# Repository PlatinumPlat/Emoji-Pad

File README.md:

# Emoji-Pad

# Description & Features
Emoji-Pad is a 5 key macropad with 2 WS2812B Leds. It uses KMK firmware and has five buttons for typing the common emojis: '👍', '🤣', '💀', '🔥', and '😃'.

# Bill Of Materials
Everything you need to make the Emoji-Pad!
- 5x Cherry MX Switches
- 4x M3x5x4 Heatset inserts
- 2x WS2812B LEDs
- 1x XIAO RP2040
- 1x Case (2 printed parts)

# Firmware
The Emoji-Pad uses KMK firmware (in Circuit Python) for all its components.
The 5 keys currently act as macros.

# Screenshots
Hackpad CAD model:
The top and bottom of the case fit together using 4 M3 Bolts and heatset inserts.

I made the Schematic and PCB in Kicad.

Schematic:

PCB:

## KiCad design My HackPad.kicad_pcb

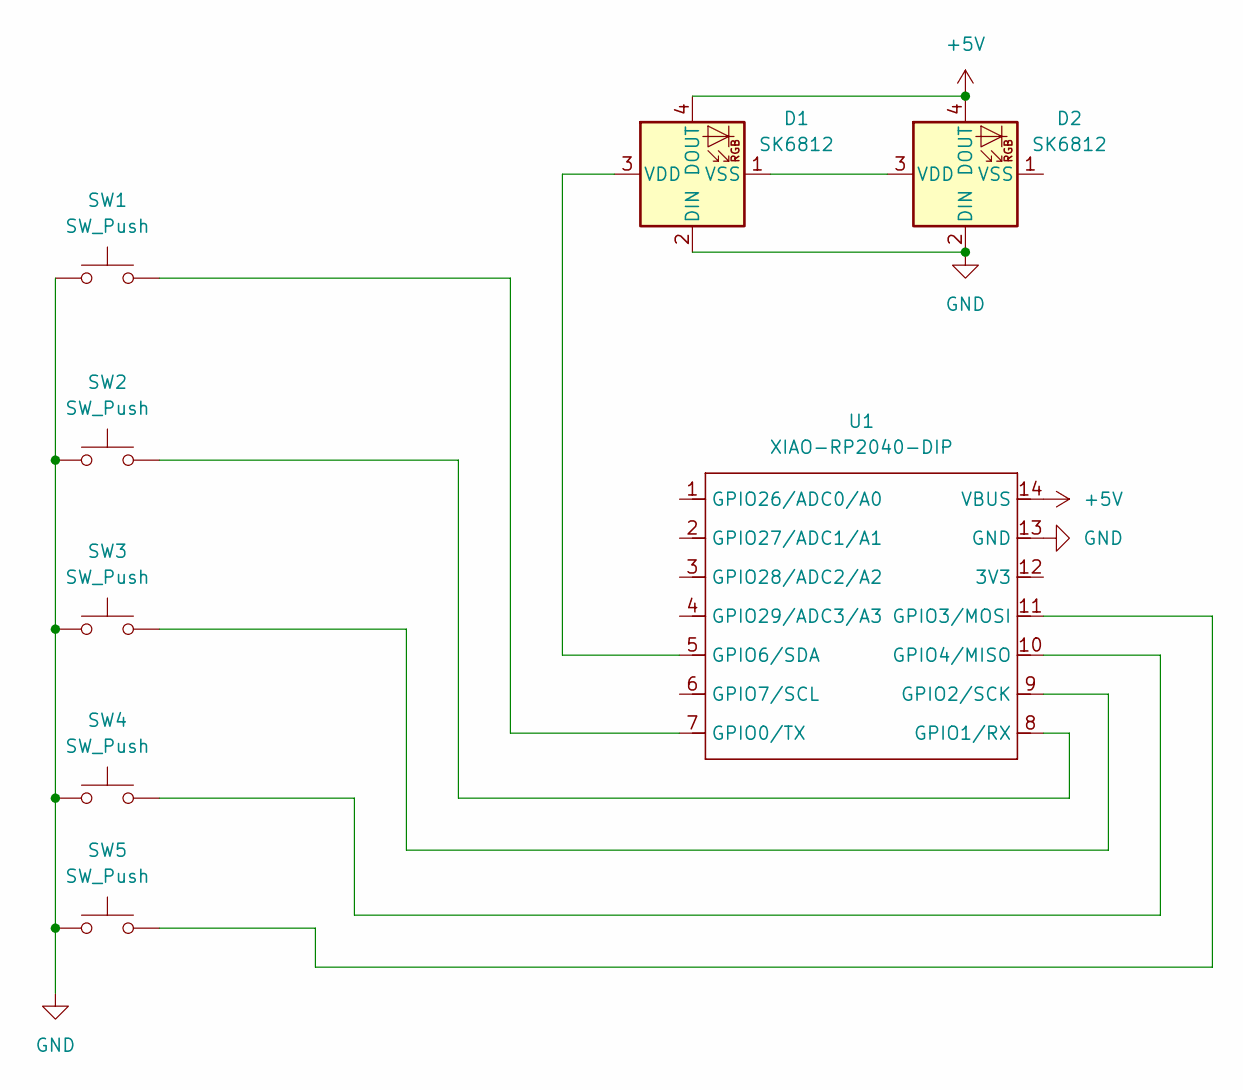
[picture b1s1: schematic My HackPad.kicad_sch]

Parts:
D1, D2: SK6812; LED_SK6812MINI_PLCC4_3.5x3.5mm_P1.75mm
SW1, SW2, SW3, SW4, SW5: SW_Push; SW_Cherry_MX_1.00u_PCB
U1: XIAO-RP2040-DIP

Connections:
+5V: D1.4 (DOUT), D2.4 (DOUT), U1.14 (VBUS)
GND: D1.2 (DIN), D2.2 (DIN), SW1.1, SW2.1, SW3.1, SW4.1, SW5.1, U1.13 (GND)
unnamed: D1.3 (VDD), U1.5 (GPIO6/SDA)
unnamed: D1.1 (VSS), D2.3 (VDD)
unnamed: SW1.2, U1.7 (GPIO0/TX)
unnamed: SW2.2, U1.8 (GPIO1/RX)
unnamed: SW3.2, U1.9 (GPIO2/SCK)
unnamed: SW5.2, U1.11 (GPIO3/MOSI)
unnamed: SW4.2, U1.10 (GPIO4/MISO)

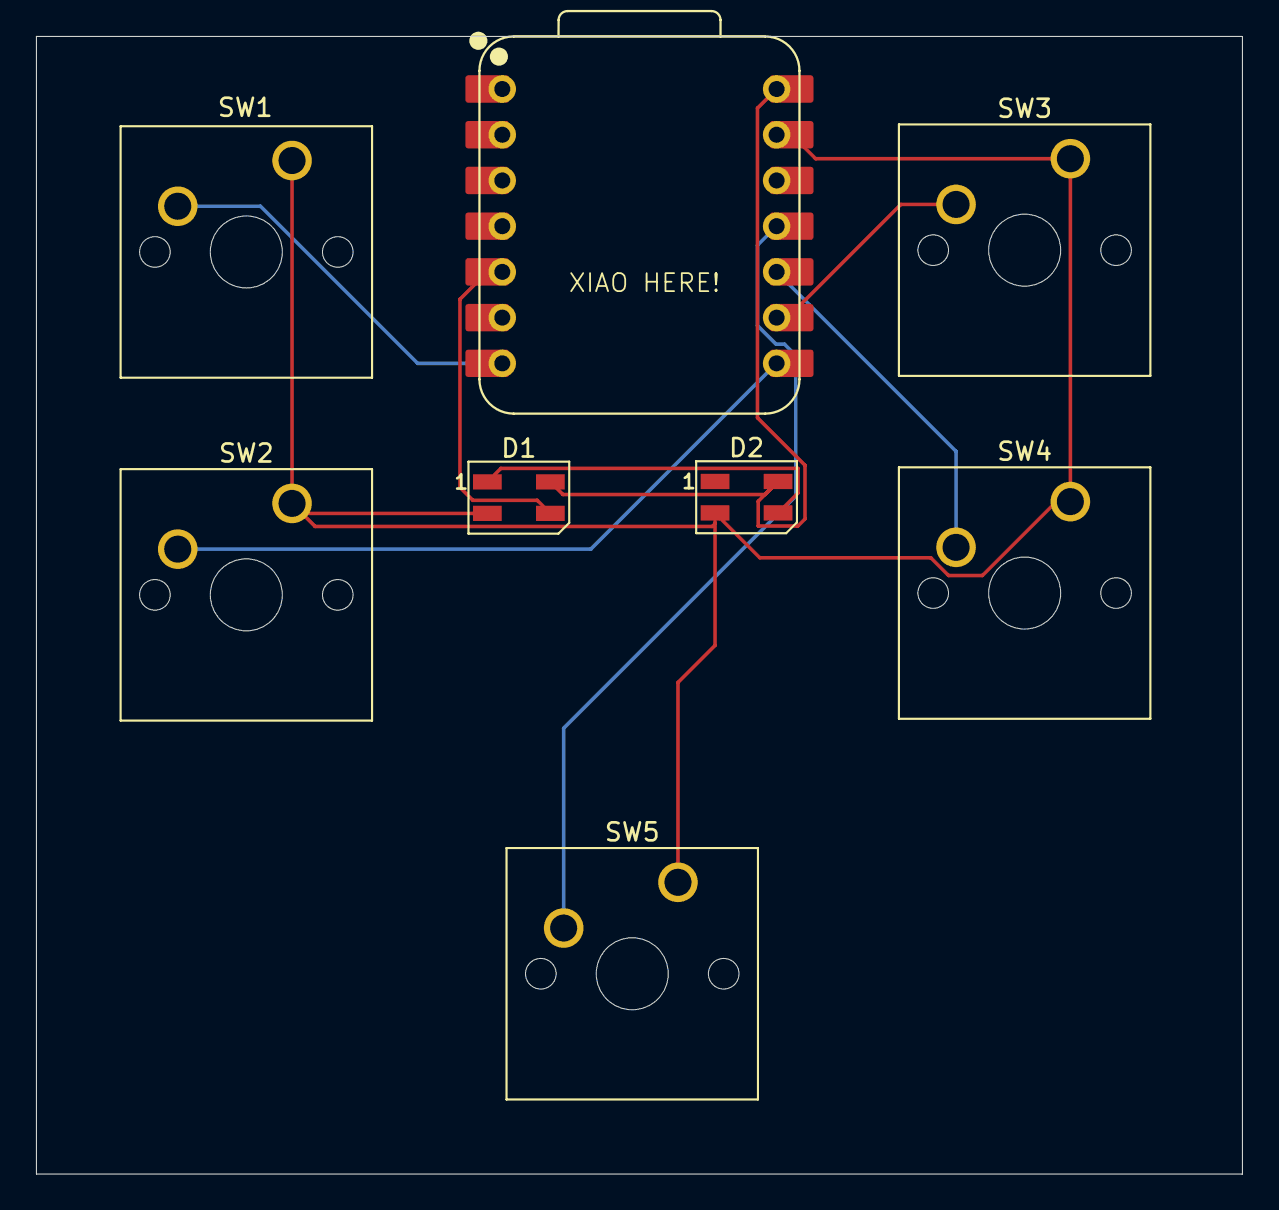
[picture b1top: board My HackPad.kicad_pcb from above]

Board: 2 copper layers, 67.0 x 63.2 mm, 8 parts (0 on the bottom side), 9 nets.

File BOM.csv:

"Id";"Designator";"Footprint";"Quantity";"Designation";"Supplier and ref";
1;"SW1,SW5,SW2,SW4,SW3";"SW_Cherry_MX_1.00u_PCB";5;"SW_Push";;;
2;"D1,D2";"LED_SK6812MINI_PLCC4_3.5x3.5mm_P1.75mm";2;"SK6812";;;
3;"U1";"XIAO-RP2040-DIP";1;"XIAO-RP2040-DIP";;;

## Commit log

2025-07-09 yipee
2025-07-09 firmware
2025-07-09 rename
2025-07-09 combined emojipad
2025-07-10 correct firmware
2025-07-10 organization + BOM
2025-07-11 screenshots
